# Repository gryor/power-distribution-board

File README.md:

Power Distribution Board
========================

Power distribution board for a drone

Image
===

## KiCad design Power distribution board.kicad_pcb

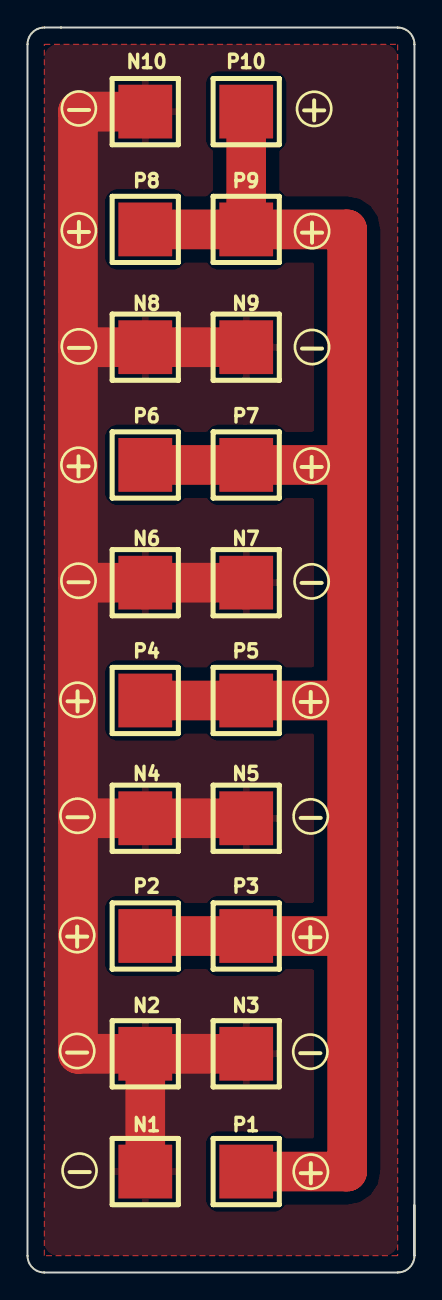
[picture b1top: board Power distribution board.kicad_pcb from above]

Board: 2 copper layers, 29.2 x 94.0 mm, 20 parts (0 on the bottom side), 2 nets.

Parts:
N1, N2, N3, N4, N5, N6, N7, N8, N9, N10: CONN_1; 1PIN_SMD
P1, P2, P3, P4, P5, P6, P7, P8, P9, P10: CONN_1; 1PIN_SMD

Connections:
+BATT: P1.1, P2.1, P3.1, P4.1, P5.1, P6.1, P7.1, P8.1, P9.1, P10.1
GND: N1.1, N2.1, N3.1, N4.1, N5.1, N6.1, N7.1, N8.1, N9.1, N10.1

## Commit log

2014-12-06 Added printed results
2014-12-06 Added image
2014-12-06 Added image to the readme
2014-12-06 Added plus and minus labels
2014-12-06 Other than front copper are not mirrored
2014-12-06 Fixed silkscreen
2014-12-06 Removed battery label for more universal outlook
